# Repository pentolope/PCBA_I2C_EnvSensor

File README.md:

# I²C Environmental Sensor Pod

A compact 3.3 V I²C sensor pod for temperature, humidity, pressure and ambient light on a 4-pin 3V3/GND/SDA/SCL host connector.

This repository holds the design problem for a compact 3.3 V I²C environmental sensor pod that measures temperature, humidity, pressure and ambient light and connects to a host through a 4-pin connector carrying 3V3, GND, SDA and SCL. The brief fixes the measurands, the supply rail, the bus type, the connector pin count and signal set, the need for address-selection or isolation where needed so the sensors can coexist, two placement constraints (heat-generating parts away from the temperature/humidity sensor, sensing elements reasonably exposed to ambient air), and it sets a low-cost two-layer assembly from readily available parts as the target. Everything else is open: no sensor parts, connector part, footprint or mating style, pull-up values, bus speed, current budget, board outline, stackup detail, protection scheme or test strategy is named. This is a detail-2 brief, so most of the architecture and all component selection belong to the design agent, which must make and document those choices rather than treat them as pre-decided.

> **This board has not been designed.** There is no schematic, no layout and no
> part selection here — only the brief, a reading of the brief, and the
> scaffolding a design run needs. That is the intended state of this repository,
> not a gap in it.

## What the brief fixes, and what it leaves open

The brief pins down 11 requirements and deliberately leaves
18 decisions to whoever designs the board. The `Source` column says
which is which: `brief` is quoted from [BRIEF.md](BRIEF.md), `metadata` comes
from the benchmark catalogue, and `open` means the brief does not fix it.

| Aspect | Value | Source |
|---|---|---|
| Function | Compact I²C sensor pod measuring temperature, humidity, pressure and ambient light | brief |
| Supply rail | 3.3 V | brief |
| Host interface | I²C (SDA/SCL) to a host | brief |
| Host connector | 4-pin, carrying 3V3, GND, SDA and SCL; connector type/part/pitch not fixed | brief |
| Bus coexistence | Address-selection or isolation included where needed so the sensors can coexist | brief |
| Thermal placement | Heat-generating parts kept away from the temperature/humidity sensor | brief |
| Sensing-element exposure | Sensing elements reasonably exposed to ambient air | brief |
| Cost and part availability | Low-cost assembly using readily available parts | brief |
| Assembly target | Two-layer assembly, stated by the brief as the target | brief |
| Likely layer count | 2 | metadata |
| Benchmark class | Category: sensor; difficulty 1/5; brief detail 2/5 | metadata |
| Primary stressors | sensor placement, I2C pullups, low-power, connector/pinout | metadata |
| Sensor devices and part numbers | Not fixed by the brief — design agent's choice | open |
| Board outline, dimensions and mounting | Not fixed by the brief beyond "compact" — design agent's choice | open |
| Connector mating style (cable, board-to-board, header into a carrier) | Not fixed by the brief, which names only the pin count and the four signals — design agent's choice | open |

The full split, with the verbatim brief text substantiating every fixed
requirement, is in [board/requirements.md](board/requirements.md) and
machine-readably in [board/requirements.json](board/requirements.json).

**Missing details are design freedom, not permission to fabricate unstated user
requirements.** A choice the brief left open is recorded as a decision, with its
reasoning — never promoted into a requirement.

## Benchmark position

| | |
|---|---|
| Benchmark id | 2 of 32 |
| Category | sensor |
| Difficulty | 1 / 5 |
| Brief detail | 2 / 5 |
| Likely layer count | 2 |
| Primary stressors | sensor placement, I2C pullups, low-power, connector/pinout |

This is a difficulty 1/5 board with a sparse brief (detail 2/5), which tests whether an agent can produce a clean, buildable two-layer sensor design without inventing requirements the brief never stated. The named stressors — sensor placement, I2C pullups, low-power and connector/pinout — are exactly the four places where a plausible-sounding but unsubstantiated answer is easy to write: thermal and airflow separation for the temp/humidity element, a pull-up value justified by an actual bus-capacitance and rise-time budget, current draw claimed against a real datasheet, and a connector choice that is argued rather than copied from a familiar 4-pin ecosystem. It also checks discipline about multi-device I²C addressing, since the brief requires the sensors to coexist but names no devices and no addresses.

This repository is one of thirty-two. The suite, the protocol and the results
live in [PCBA_AutoDesignAndTest_Bench](https://github.com/pentolope/PCBA_AutoDesignAndTest_Bench).

## Repository layout

| Path | Contents |
|---|---|
| `BRIEF.md` | the supplied brief — authoritative, preserved byte for byte, never edited |
| `board/requirements.md` | what the brief fixes, what it leaves open, and where decisions get recorded |
| `board/requirements.json` | the same split, machine-readable, each fixed requirement bound to brief text |
| `board/manifest.template.json` | the toolkit's minimum manifest, pre-filled for this board |
| `board/toolchain.json` | where this board's build finds KiCad and the router |
| `benchmark/metadata.json` | the supplied catalogue entry — category, difficulty, detail, stressors |
| `docs/architecture.md` | the decisions this board must make, as questions, unanswered |
| `docs/sources.md` | the classes of evidence the design will have to cite |
| `docs/status.md` | what exists, what does not, and what is deliberately absent |
| `candidates/` | disposable search output, ignored by Git |
| `.claude/skills/` | the accountability-review skill [CLAUDE.md](CLAUDE.md) requires before a push |
| `tooling/PCBA_AutoDesignAndTest` | the shared verification/routing/release toolkit, as a pinned submodule |

## Getting the repository

The toolkit is a submodule and carries KiCad Routing Tools as a submodule of its
own, so clone recursively:

```bash
git clone --recursive https://github.com/pentolope/PCBA_I2C_EnvSensor.git
```

```bash
git submodule update --init --recursive
```

## Designing the board

Generic verification, routing and release logic is **not** written here. It is
consumed from `tooling/PCBA_AutoDesignAndTest`, which is board-agnostic by
construction and must stay that way; this repository owns the board and nothing
else. Start from
[the toolkit's onboarding guide](tooling/PCBA_AutoDesignAndTest/examples/onboarding.md),
and see [CLAUDE.md](CLAUDE.md) for the rules a design run works under.

```bash
python3 tooling/PCBA_AutoDesignAndTest/run.py preflight
```

## Brief integrity

`BRIEF.md` SHA-256 `019c2710442d044925aca61fa96e84416cafc10bbb07df4bdcfe612aea375544`

Every quotation in `board/requirements.json` is bound to those exact bytes. If
the brief ever changes, the bindings are stale by construction — which is the
point of recording the digest.

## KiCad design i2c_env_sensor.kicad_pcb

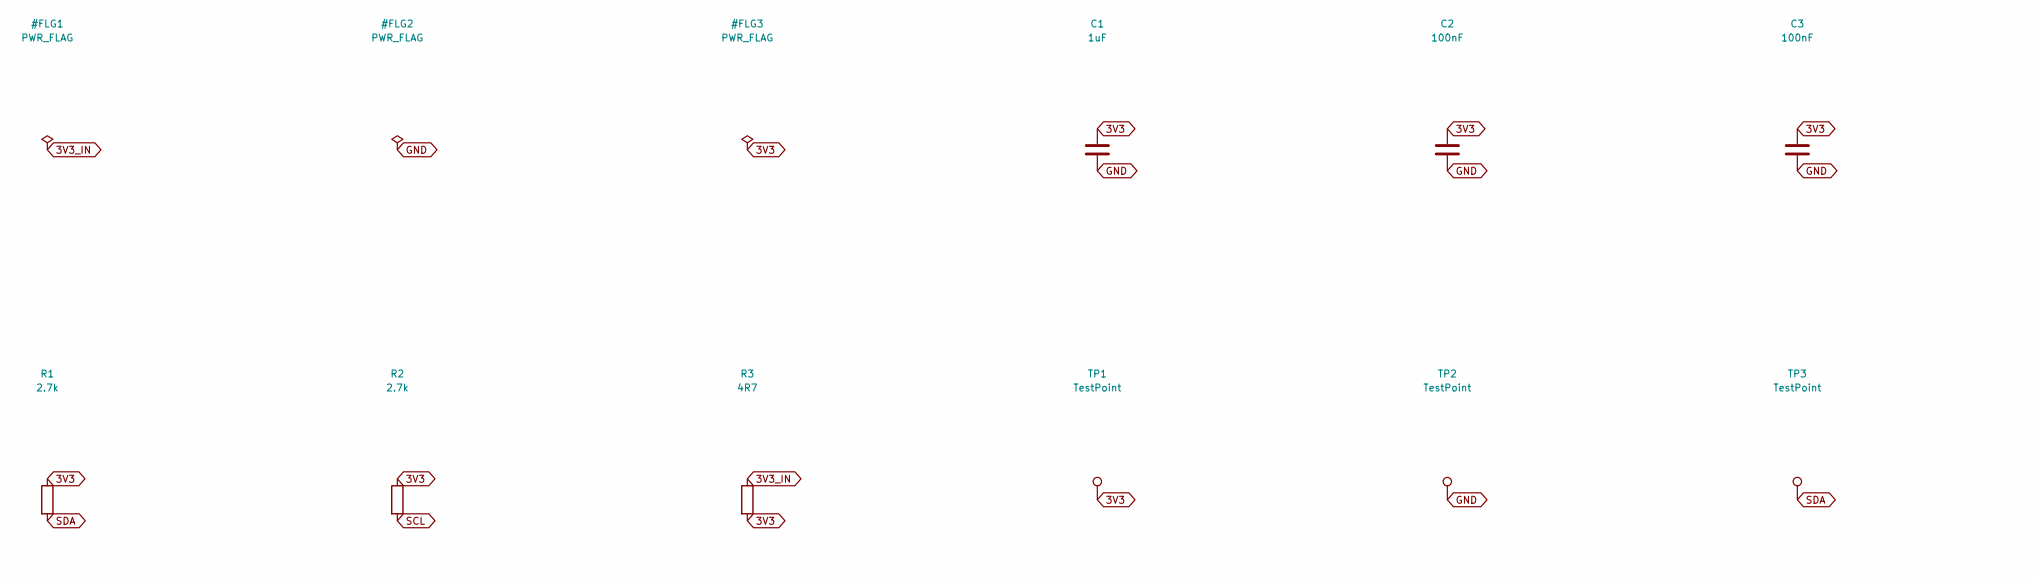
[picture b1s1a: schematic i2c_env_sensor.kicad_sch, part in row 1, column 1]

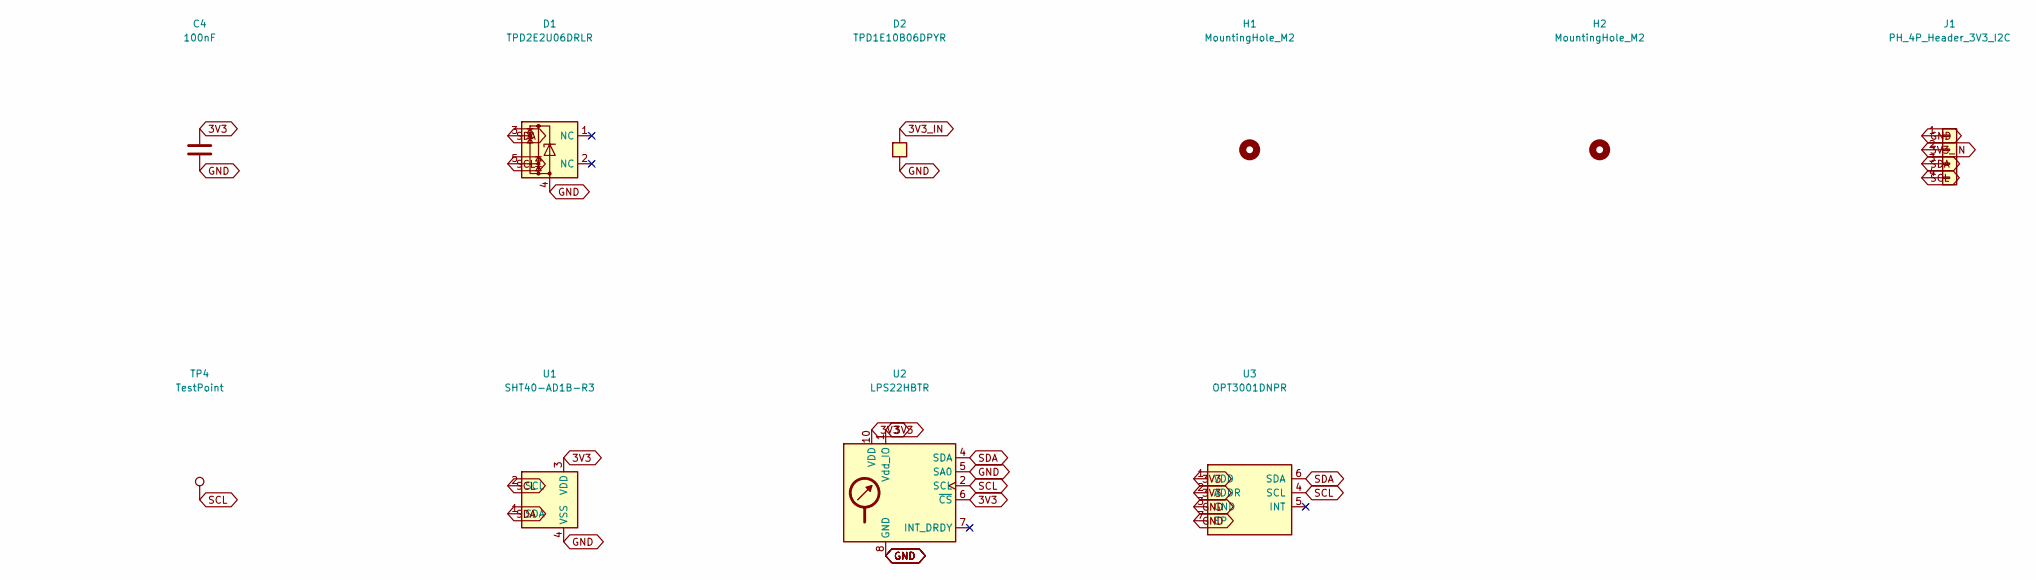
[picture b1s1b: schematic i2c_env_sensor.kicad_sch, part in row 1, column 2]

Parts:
C1: 1uF; C_0603_1608Metric; MPN CL10A105KB8NNNC; LCSC C15849
C2, C3, C4: 100nF; C_0402_1005Metric; MPN CL05B104KO5NNNC; LCSC C1525
D1: TPD2E2U06DRLR; SOT-553; MPN TPD2E2U06DRLR; LCSC C1972959
D2: TPD1E10B06DPYR; Texas_X1SON-2_1.1x0.7mm_P0.7mm; MPN TPD1E10B06DPYR; LCSC C48260
H1, H2: MountingHole_M2; MountingHole_2.2mm_M2_DIN965
J1: PH_4P_Header_3V3_I2C; JST_PH_S4B-PH-K_1x04_P2.00mm_Horizontal; MPN S4B-PH-K-S(LF)(SN); LCSC C157926
R1, R2: 2.7k; R_0402_1005Metric; MPN RC0402FR-072K7L; LCSC C138017
R3: 4R7; R_0402_1005Metric; MPN CRCW04024R70FKED; LCSC C482197
TP1, TP2, TP3, TP4: TestPoint; TestPoint_Pad_D1.0mm
U1: SHT40-AD1B-R3; Sensirion_DFN-4_1.5x1.5mm_P0.8mm_SHT4x_NoCentralPad; MPN SHT40-AD1B-R3; LCSC C2848306
U2: LPS22HBTR; ST_HLGA-10_2x2mm_P0.5mm_LayoutBorder3x2y; MPN LPS22HBTR; LCSC C94049
U3: OPT3001DNPR; Texas_USON-6-1EP_2x2mm_P0.65mm_EP0.65x1.35mm; MPN OPT3001DNPR; LCSC C90462

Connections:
3V3: C1.1, C2.1, C3.1, C4.1, R1.1, R2.1, R3.2, TP1.1, U1.3 (VDD), U2.1 (Vdd_IO), U2.6 (~CS), U2.10 (VDD), U3.1 (VDD), U3.2 (ADDR)
3V3_IN: D2.2 (A2), J1.2, R3.1
GND: C1.2, C2.2, C3.2, C4.2, D1.4, D2.1 (A1), J1.1, TP2.1, U1.4 (VSS), U2.3 (GND), U2.5 (SA0), U2.8 (GND), U2.9 (GND), U3.3 (GND), U3.7 (EP)
SCL: D1.5, J1.4, R2.2, TP4.1, U1.2 (SCL), U2.2 (SCL), U3.4 (SCL)
SDA: D1.3, J1.3, R1.2, TP3.1, U1.1 (SDA), U2.4 (SDA), U3.6 (SDA)

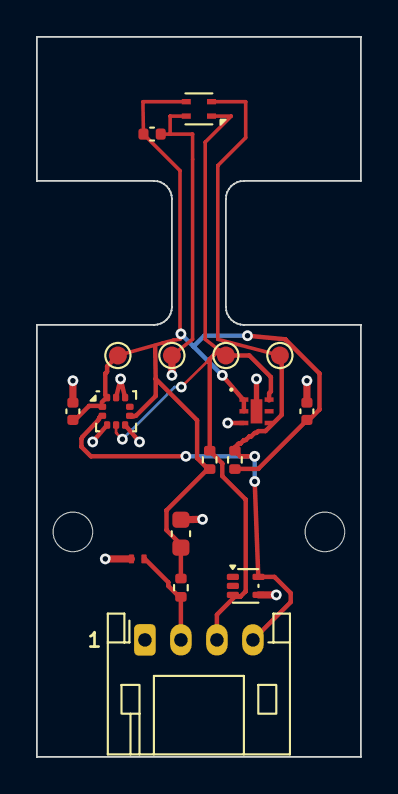
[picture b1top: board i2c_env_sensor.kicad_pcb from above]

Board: 2 copper layers, 18.0 x 40.0 mm, 19 parts (0 on the bottom side), 5 nets.
